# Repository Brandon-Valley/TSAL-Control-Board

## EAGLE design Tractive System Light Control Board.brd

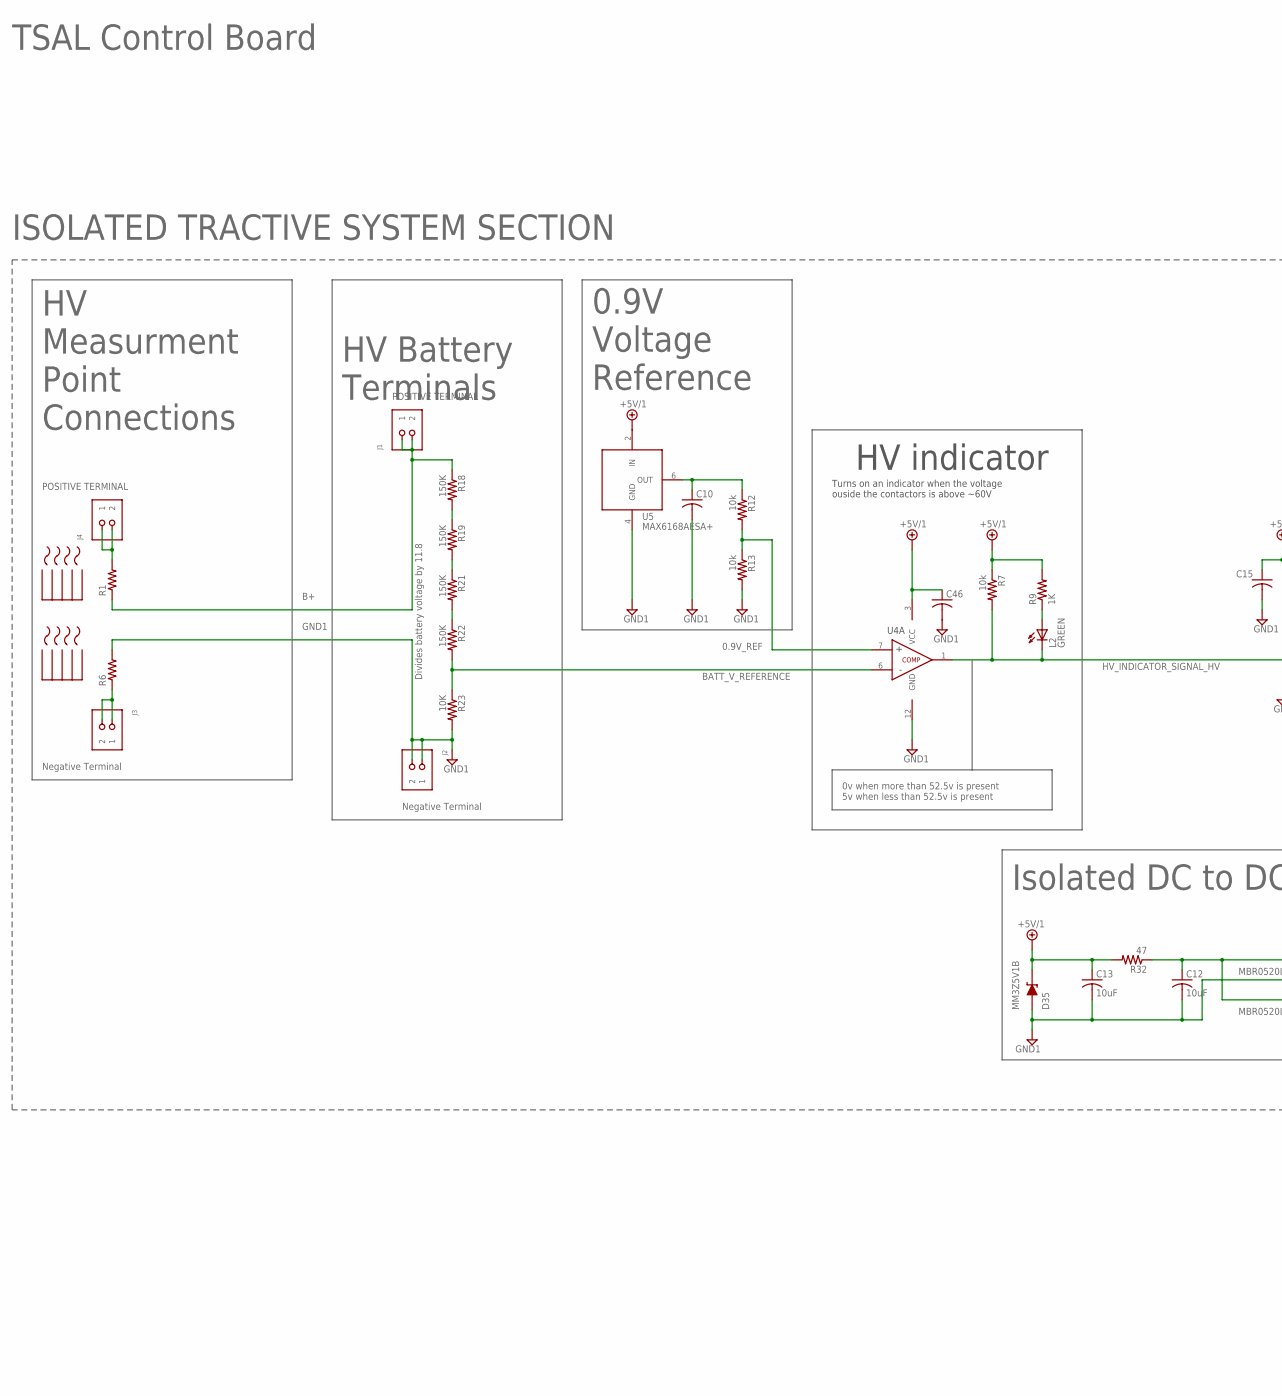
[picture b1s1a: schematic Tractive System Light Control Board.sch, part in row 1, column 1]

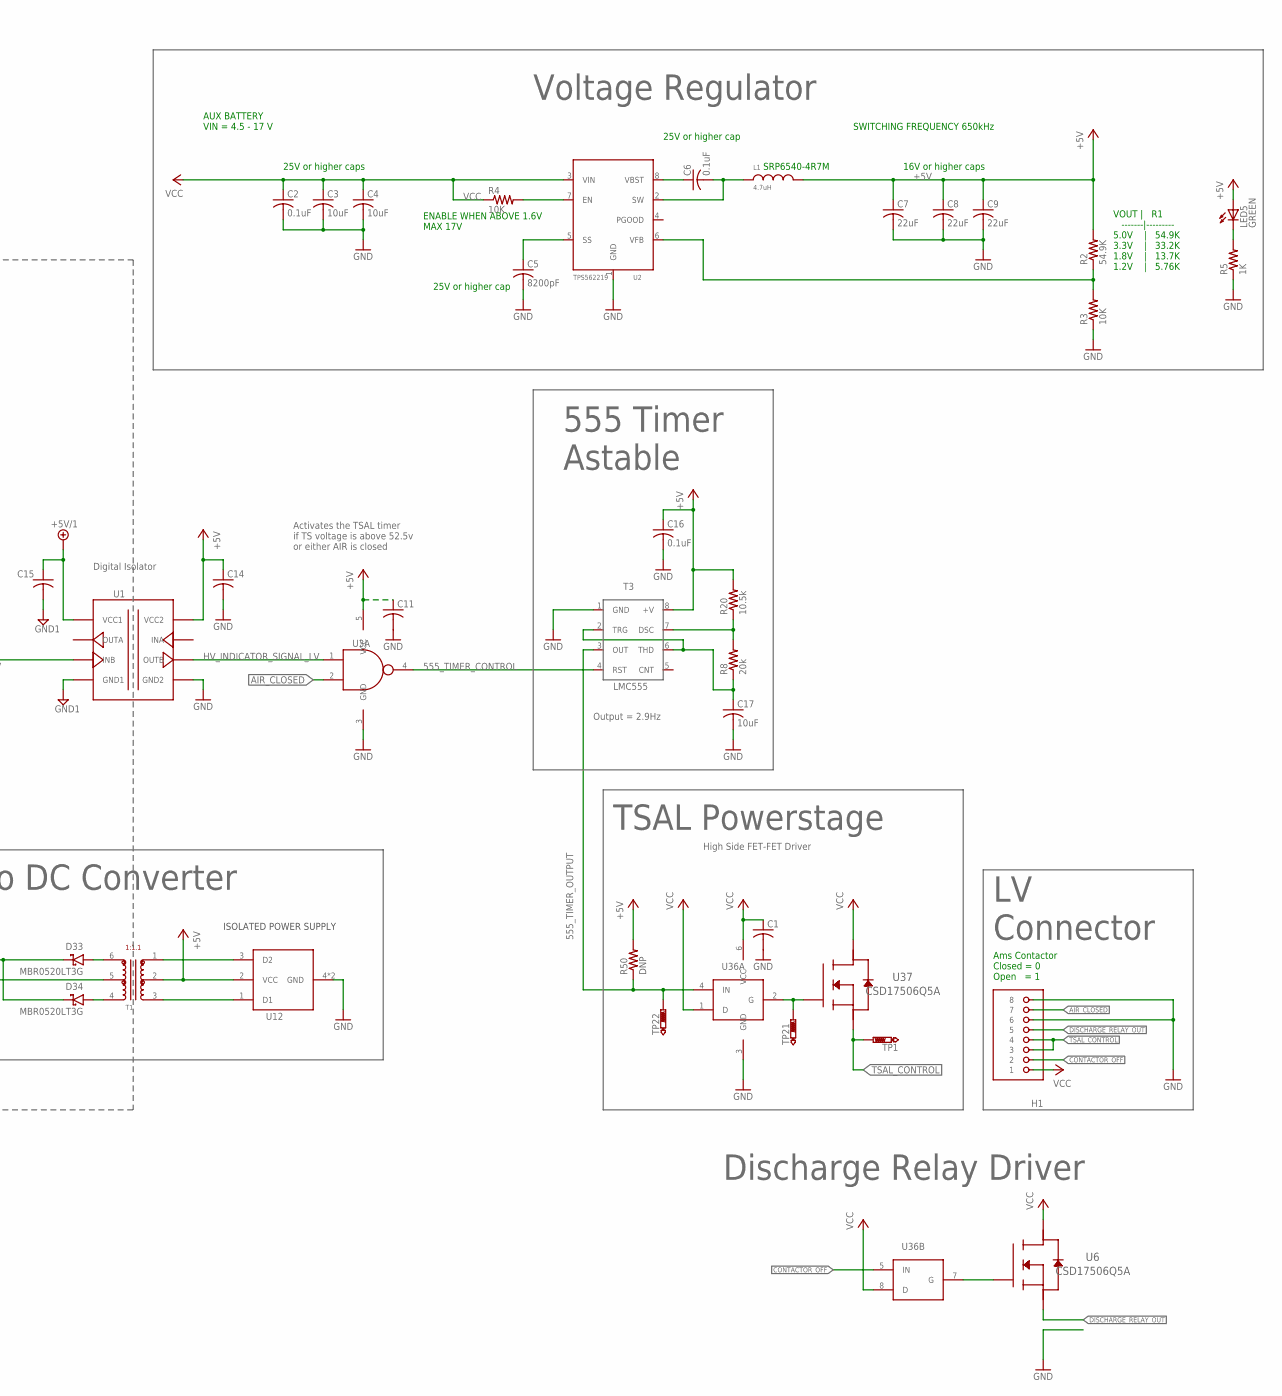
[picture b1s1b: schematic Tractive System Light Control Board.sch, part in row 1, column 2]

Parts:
C1, C10, C11, C14, C15, C46: 0.1uF; C0805; MPN C1005X7R1E104K050BB
C2, C6: 0.1uF; C0805; PARTNO GRM21BR71E104KA01L
C3, C4, C17: 10uF; C0805; PARTNO GRM21BR61E106KA73L
C5: 8200pF; C0805; PARTNO C0805C822K5RACTU
C7, C8, C9: 22uF; C0805; PARTNO C2012JB1E226M125AC
C12, C13: 10uF; C0805; MPN C1005X7R1E104K050BB
C16: 0.1uF; C0805; PARTNO 08053C104KAT2A
D33, D34: MBR0520LT3G; SOD-123; PARTNO MBR0520LT3G
D35: MM3Z5V1B; SOD323F; PARTNO MM3Z5V1B
H1: MOLEX_CLIKMATE-8-VERTICAL-5025841170; MOLEX-CLIKMATE-8-VERTICAL-HEADER; PARTNO 5025840870
J1, J2, J3, J4: MOLEX_CLICKMATE-2-VERTICAL; MOLEX-CLIKMATE-2-VERTICAL-HEADER; PARTNO 5025840270
L1: 4.7uH; SRP6540; PARTNO SRP6540-4R7M
L2: GREEN; CHIPLED_0805; PARTNO 598-8170-107F
LED5: GREEN; CHIPLED_0805; PARTNO 598-8170-107F
R1, R6: RTO020F10001JTE3; TO-220-2; PARTNO RTO020F10001JTE3
R2: 54.9K; R0805; PARTNO ERA-6AEB5492V
R3, R4, R23: 10K; R0805; PARTNO ERJ-6ENF1002V
R5, R9: 1K; R0805; PARTNO ERJ-6ENF1001V
R7, R12, R13: 10k; R0805; PARTNO ERJ-6ENF1002V
R8: 20k; R0805; PARTNO ERJ-6ENF2002V
R18, R19, R21, R22: 150K; R0805; PARTNO ERJ-6ENF1503V
R20: 10.5k; R0805; PARTNO ERJ-6ENF1052V
R32: 47; R0805; PARTNO ERA-6AEB470V
R50: DNP; R0805
T1: 750313734; WURTH-750313734; PARTNO 750313734
T3: LMC555; PARTNO LMC555CMM/NOPB
TP1, TP21, TP22: PTR1TP20R; TP20R
U1: ISO7221; ISO722X; PARTNO ISO7221CDR
U2: TPS562219; PARTNO TPS562219DDFT
U3: SN74LVC1G00DRL; LITTLE_LOGIC_BASIC_DRL; PARTNO SN74LVC1G00DRLR
U4: LM139; D14; PARTNO LM139DR
U5: MAX6168AESA+; SOIC-8; PARTNO MAX6168AESA+
U6: CSD17506Q5A; SON_5X6
U12: SN6501DBVR; SN6501DBV; PARTNO SN6501DBVR
U36: LTC1155; LT-SOL8; PARTNO LTC1155CS8#PBF
U37: CSD17506Q5A; SON_5X6; PARTNO CSD17506Q5A
U$1, U$2: 581002B02500G; AAVID-581X; PARTNO 581002B02500G

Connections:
0.9V_REF: R12.2, R13.1, U4.7 (+)
1.8V_REF: C10.1, R12.1, U5.6 (OUT)
555_TIMER_CONTROL: T3.4 (RST), U3.4 (OUT)
555_TIMER_OUTPUT: R50.1, T3.3 (OUT), TP22.TP, U36.4 (IN)
+5V: C7.1, C8.1, C9.1, C11.1, C14.1, C16.1, L1.P$2, LED5.A, R2.2, R20.2, R50.2, T1.2, T3.8 (+V), U1.P$8 (VCC2), U3.5 (VCC), U12.2 (VCC)
+5V/1: C13.1, C15.1, C46.1, D35.CATHODE, R7.1, R9.2, R32.2, U1.P$1 (VCC1), U4.3 (VCC), U5.2 (IN)
AIR_CLOSED: H1.7, U3.2 (IN2)
B+: J1.1, J1.2, R1.P$1, R18.1
BATT_V_REFERENCE: R22.2, R23.1, U4.6 (-)
CONTACTOR_OFF: H1.2, U36.5 (IN)
DISCHARGE_RELAY_OUT: H1.5, U6.1 (S), U6.2 (S), U6.3 (S)
GND: C1.2, C2.2, C3.2, C4.2, C5.2, C7.2, C8.2, C9.2, C11.2, C14.2, C16.2, C17.2, H1.6, H1.8, R3.1, R5.1, T3.1 (GND), U1.P$5 (GND2), U2.1 (GND), U3.3 (GND), U12.4 (GND), U12.5 (GND), U36.3 (GND)
GND1: C10.2, C12.2, C13.2, C15.2, C46.2, D35.ANODE, J2.1, J2.2, R6.P$2, R13.2, R23.2, T1.5, U1.P$4 (GND1), U4.12 (GND), U5.4 (GND)
HV_INDICATOR_SIGNAL_HV: L2.C, R7.2, U1.P$3 (INB), U4.1 (OUT)
HV_INDICATOR_SIGNAL_LV: U1.P$6 (OUTB), U3.1 (IN1)
unnamed: R4.2, U2.7 (EN)
unnamed: LED5.C, R5.2
unnamed: TP21.TP, U36.2 (G), U37.4 (G)
unnamed: L2.A, R9.1
unnamed: J4.1, J4.2, R1.P$2
unnamed: J3.1, J3.2, R6.P$1
unnamed: U6.4 (G), U36.7 (G)
unnamed: R8.2, R20.1, T3.7 (DSC)
unnamed: C17.1, R8.1, T3.2 (TRG), T3.6 (THD)
unnamed: R18.2, R19.1
unnamed: R19.2, R21.1
unnamed: R21.2, R22.1
unnamed: T1.1, U12.3 (D2)
unnamed: T1.3, U12.1 (D1)
unnamed: D33.A, T1.6
unnamed: C12.1, D33.K, D34.K, R32.1
unnamed: D34.A, T1.4
SS_5V1: C5.1, U2.5 (SS)
SW_5V2: C6.2, L1.P$1, U2.2 (SW)
TSAL_CONTROL: H1.3, H1.4, TP1.TP, U37.1 (S), U37.2 (S), U37.3 (S)
VBST_5V1: C6.1, U2.8 (VBST)
VCC: C1.1, C2.1, C3.1, C4.1, H1.1, R4.1, U2.3 (VIN), U6.5 (D), U6.6 (D), U6.7 (D), U6.8 (D), U6.PAD (D), U6.PAD1 (D), U6.VIA1 (D), U6.VIA2 (D), U6.VIA3 (D), U6.VIA4 (D), U6.VIA5 (D), U6.VIA6 (D), U6.VIA7 (D), U6.VIA8 (D), U6.VIA9 (D), U36.1 (D), U36.6 (VCC), U36.8 (D), U37.5 (D), U37.6 (D), U37.7 (D), U37.8 (D), U37.PAD (D), U37.PAD1 (D), U37.VIA1 (D), U37.VIA2 (D), U37.VIA3 (D), U37.VIA4 (D), U37.VIA5 (D), U37.VIA6 (D), U37.VIA7 (D), U37.VIA8 (D), U37.VIA9 (D)
VFB_5V1: R2.1, R3.2, U2.6 (VFB)

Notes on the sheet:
HV indicator
Turns on an indicator when the voltage ouside the contactors is above ~60V
555 Timer Astable
High Side FET-FET Driver
TSAL Powerstage
Ams Contactor Closed = 0 Open = 1
AUX BATTERY VIN = 4.5 - 17 V
VOUT | R1 -------|--------- 5.0V | 54.9K 3.3V | 33.2K 1.8V | 13.7K 1.2V | 5.76K
SRP6540-4R7M
SWITCHING FREQUENCY 650kHz
ENABLE WHEN ABOVE 1.6V MAX 17V
25V or higher caps
25V or higher cap
16V or higher caps
Divides battery voltage by 11.8
ISOLATED POWER SUPPLY
Isolated DC to DC Converter
Digital Isolator
Voltage Regulator
TSAL Control Board
Output = 2.9Hz
Activates the TSAL timer if TS voltage is above 52.5v or either AIR is closed
0v when more than 52.5v is present 5v when less than 52.5v is present
POSITIVE TERMINAL
Negative Terminal
ISOLATED TRACTIVE SYSTEM SECTION
HV Battery Terminals
HV Measurment Point Connections
LV Connector
0.9V Voltage Reference
Discharge Relay Driver

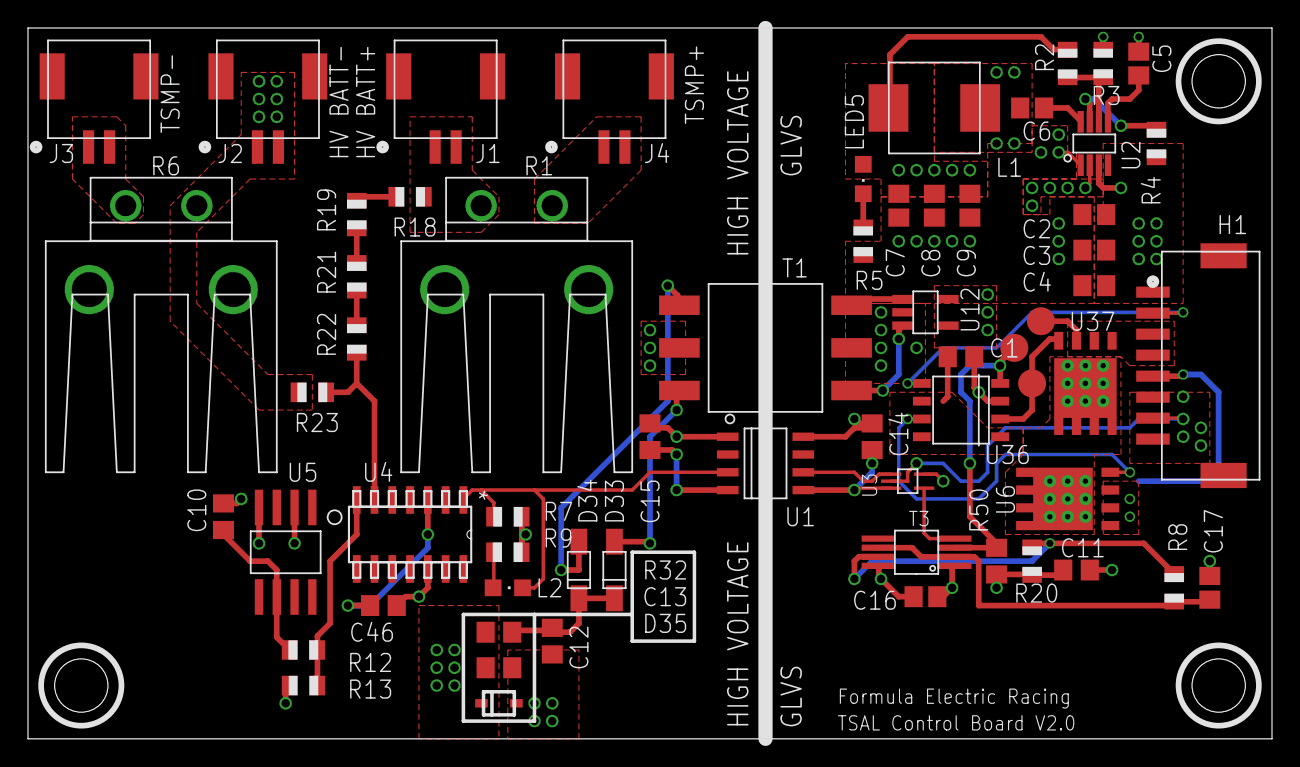
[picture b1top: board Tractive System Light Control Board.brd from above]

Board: 4 copper layers, 88.9 x 50.8 mm, 64 parts (0 on the bottom side), 38 nets.

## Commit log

2016-01-04 First Commit: This PCB will control the Tractive System Active Light (TSAL). Light will flash continuously while either there is 60V or more on the high side (when the battery is on), or when a signa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
2016-01-10 Added 55 Timer schematics and DC DC Converter
2016-03-10 Done, ready to start board, changed name to TSAL Control Board
2016-03-10 Mid-design change, about to start deleting things
2016-03-11 Schematic Done
2016-03-13 Layout Done: Need graphic for HV, maybe logo in bottom right corner?
2016-03-17 Reconfigured the schematic to improve functionality and readability
2016-03-17 Changed RC values for 555 timer
2016-03-17 Added resistors and heat sink to schematic, about to make changes
2016-03-17 Made changes, about to start finishing layout
2016-03-17 Ran ERC, made changes, about to start layout
2016-03-17 Fixed small schematic errors, about to start layout
2016-03-18 Done with layout, about to start BOM
2016-03-18 Layout done
2016-03-18 Small Layout Changes, about to start BOM
2016-03-18 BOM Done, files next
2016-03-20 BOM Done, about to generate files
2016-03-23 Fixed BOM, added MM3Z5V1B
2016-03-26 Fixed comparator and BOM, about to generate files
2016-03-26 DONE: added files, ready for order
2016-03-27 A few minor layout tweaks. Regenerated gerbers and BOM
2016-04-18 Update gitignore
2016-04-20 Fixed 10k Resistors- TSAL Control Board V2.0- Ready To Order
2016-04-20 Updated BOM, ready to order... again
2016-04-20 Fixed 10K resistor holes- now 1.5 mm, Cams done, ready for order
2016-04-20 Generated BOM
2016-05-04 Added missing pad connections on high volt side,
2016-05-04 Fixed pads on high volt side connectors, cams made, ready for re-order
2016-05-08 Added second pin connection to hv connections, regnerated gerbers
2016-05-09 Added discharge relay driver, regen gerbers
